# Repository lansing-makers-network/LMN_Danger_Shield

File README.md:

# LMN_Danger_Shield
This is an customized version of the depricated Sparkfun Danger Shield v17

Changes.
* added foot prints for optional pull-ups to buttons. I have run across several UNO's who's internal pull-ups do not work.
* Added 3 pin header for Servo, driven by PWM on D9, which is in parallel to Cap Sense.
* added USB1881 Hall effect sensor, in parallel to TMP36. As TMP36 is out of stock at SFE.

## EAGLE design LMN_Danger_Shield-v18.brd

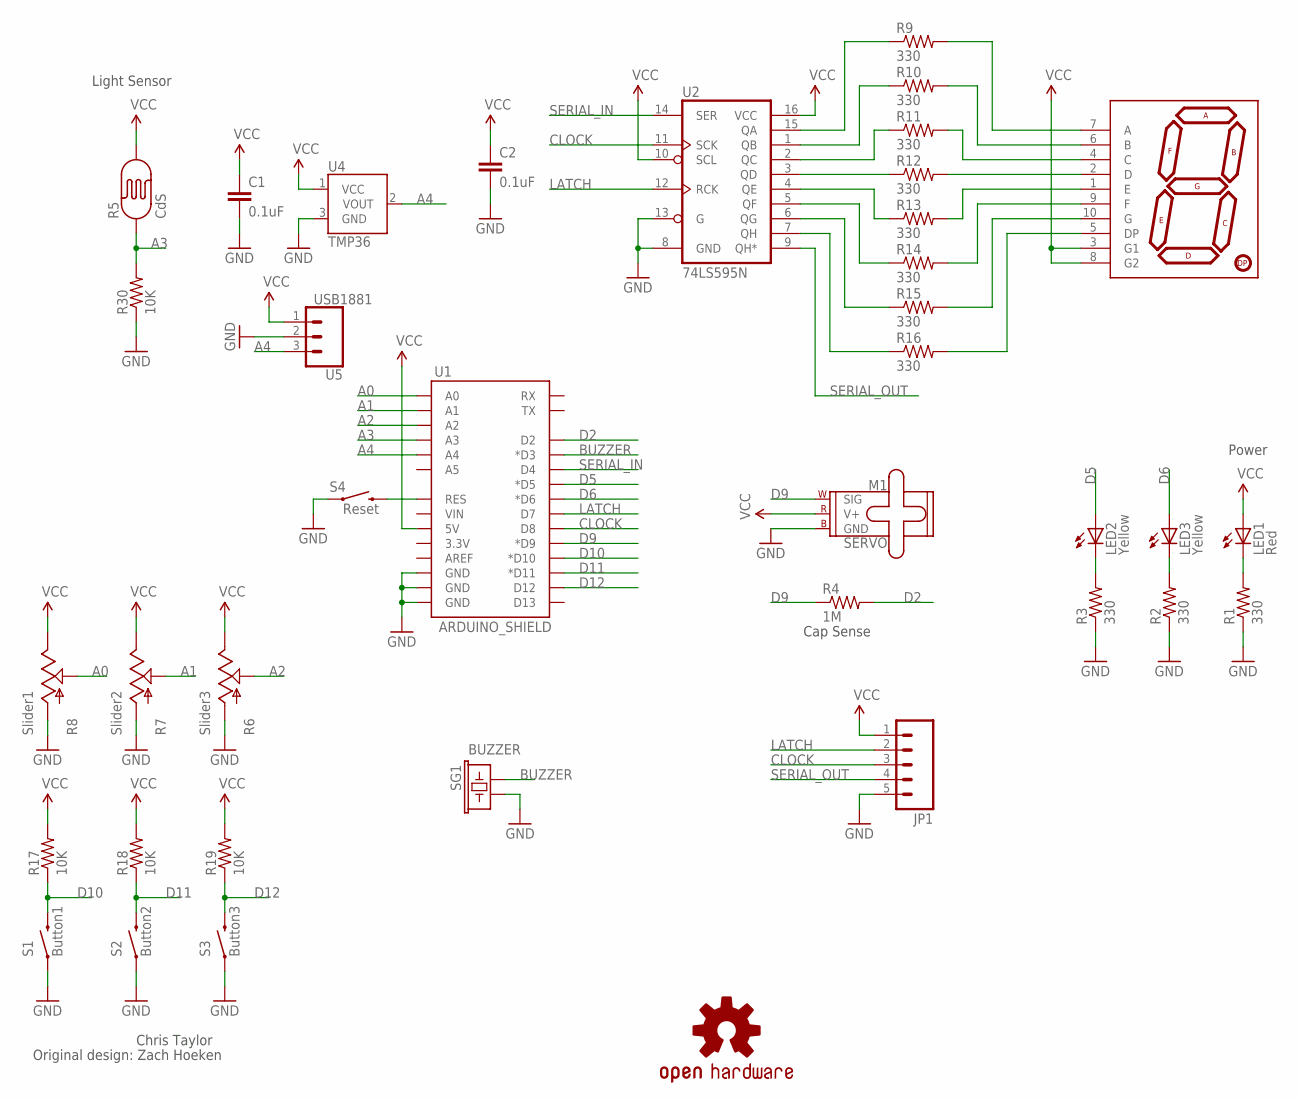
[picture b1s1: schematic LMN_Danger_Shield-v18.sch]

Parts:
C1, C2: 0.1uF; CAP-PTH-SMALL2
JP1: M05PTH; 1X05
LED1: Red; LED5MM
LED2, LED3: Yellow; LED5MM
M1: SERVO; 1X03
R1, R2, R3, R9, R10, R11, R12, R13, R14, R15, R16: 330; AXIAL-0.3
R4: 1M; AXIAL-0.3
R5: CdS; PHOTOCELL
R6: Slider3; SLIDER
R7: Slider2; SLIDER
R8: Slider1; SLIDER
R17, R18, R19, R30: 10K; AXIAL-0.3
S1: Button1; TACTILE-PTH-12MM
S2: Button2; TACTILE-PTH-12MM
S3: Button3; TACTILE-PTH-12MM
S4: Reset; TACTILE-PTH
SG1: BUZZER; BUZZER-12MM
U1: ARDUINO_SHIELD; DUEMILANOVE_VIAS
U2: 74LS595N; DIL16
U4: TMP36; TO-92
U5: USB1881; 1X03
U6: 7-SEGMENT-DISPLAY-1"-RED; 7-SEGMENT-1"PTH
U$2: OSHW-LOGOM; OSHW-LOGO-M

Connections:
A0: R8.2A (S), U1.A0
A1: R7.2A (S), U1.A1
A2: R6.2A (S), U1.A2
A3: R5.1, R30.P$2 (2), U1.A3
A4: U1.A4, U4.2 (VOUT), U5.3
BUZZER: SG1.+ (1), U1.D3 (*D3)
CLOCK: JP1.3, U1.D8, U2.11 (SCK)
D2: R4.P$2 (2), U1.D2
D5: LED2.A, U1.D5 (*D5)
D6: LED3.A, U1.D6 (*D6)
D9: M1.1 (SIG), R4.P$1 (1), U1.D9 (*D9)
D10: R17.P$1 (1), S1.3 (2), U1.D10 (*D10)
D11: R18.P$1 (1), S2.3 (2), U1.D11 (*D11)
D12: R19.P$1 (1), S3.3 (2), U1.D12
GND: C1.2, C2.2, JP1.5, M1.3 (GND), R1.P$1 (1), R2.P$1 (1), R3.P$1 (1), R6.3 (A), R7.3 (A), R8.3 (A), R30.P$1 (1), S1.1, S2.1, S3.1, S4.1, SG1.- (2), U1.GND@0 (GND), U1.GND@1 (GND), U1.GND@2 (GND), U2.8 (GND), U2.13 (G), U4.3 (GND), U5.2
LATCH: JP1.2, U1.D7, U2.12 (RCK)
unnamed: S4.3 (2), U1.RES
unnamed: R9.P$1 (1), U2.15 (QA)
unnamed: LED1.K (C), R1.P$2 (2)
unnamed: R10.P$1 (1), U2.1 (QB)
unnamed: R11.P$1 (1), U2.2 (QC)
unnamed: R12.P$1 (1), U2.3 (QD)
unnamed: R13.P$1 (1), U2.4 (QE)
unnamed: R14.P$1 (1), U2.5 (QF)
unnamed: R15.P$1 (1), U2.6 (QG)
unnamed: R16.P$1 (1), U2.7 (QH)
unnamed: R9.P$2 (2), U6.7 (A)
unnamed: R10.P$2 (2), U6.6 (B)
unnamed: R11.P$2 (2), U6.4 (C)
unnamed: R12.P$2 (2), U6.2 (D)
unnamed: R13.P$2 (2), U6.1 (E)
unnamed: R14.P$2 (2), U6.9 (F)
unnamed: R15.P$2 (2), U6.10 (G)
unnamed: R16.P$2 (2), U6.5 (DP)
unnamed: LED3.K (C), R2.P$2 (2)
unnamed: LED2.K (C), R3.P$2 (2)
SERIAL_IN: U1.D4, U2.14 (SER)
SERIAL_OUT: JP1.4, U2.9 (QH*)
VCC: C1.1, C2.1, JP1.1, LED1.A, M1.2 (V+), R5.2, R6.1 (E), R7.1 (E), R8.1 (E), R17.P$2 (2), R18.P$2 (2), R19.P$2 (2), U1.5V, U2.10 (SCL), U2.16 (VCC), U4.1 (VCC), U5.1, U6.3 (G1), U6.8 (G2)

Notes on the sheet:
Power
Light Sensor
Cap Sense
Chris Taylor
Original design: Zach Hoeken

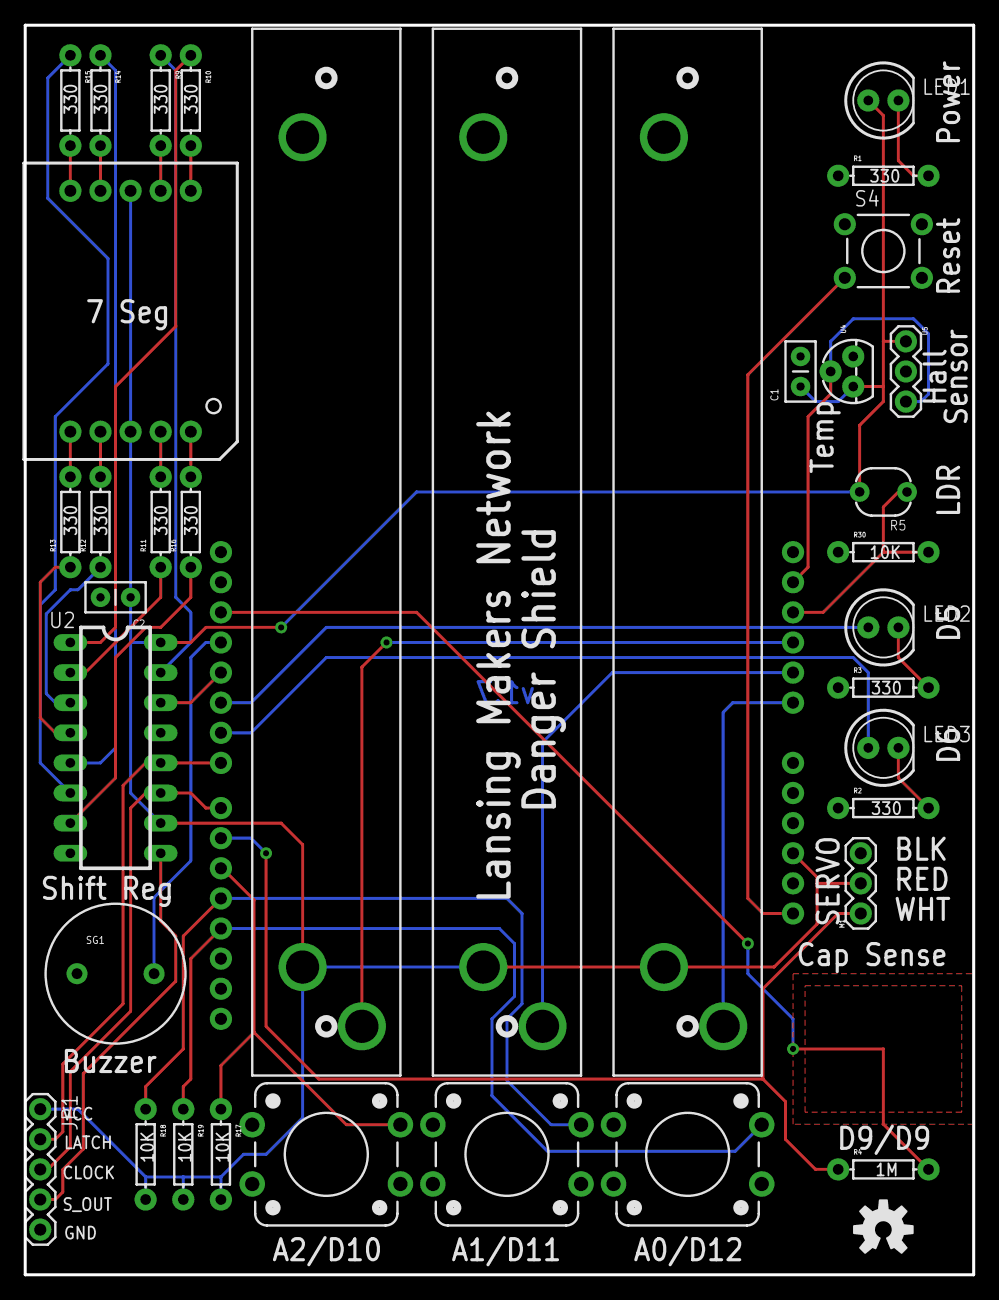
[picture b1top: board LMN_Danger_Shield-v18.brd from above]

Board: 2 copper layers, 80.0 x 105.4 mm, 39 parts (0 on the bottom side), 39 nets.

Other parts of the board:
DRILEGEND: DRILEGEND

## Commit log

2018-03-25 Initial Add of Schematic PDF
2018-03-25 added firmware and move hardware to folder

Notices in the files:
parts and their libraries:
SparkFun-Sensors: Licensing: CC v3.0 Share-Alike You are welcome to use this library for commercial purposes.
SparkFun-Connectors: Licensing: Creative Commons ShareAlike 4.0 International - https://creativecommons.org/licenses/by-sa/4.0
